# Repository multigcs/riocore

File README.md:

[LinuxCNC-RIO](https://github.com/multigcs/LinuxCNC-RIO) - rewrite

<h3 align="center">RIO</h3>

<div align="center">

</div>

---

<p align="center"> Realtime-IO for Motion-Control <br></p>

## Table of Contents
- [About](#about)
- [Disclaimer](#disclaimer)
- [Help](#help)
- [Boards](#boards)
- [Plugins/Drivers](#plugins)
- [supported Toolchains](#toolchains)
- [Getting Started](#getting_started)
- [Usage](#usage)
- [Flow](#flow)

## About 

RIO is a cost-effective and flexible alternative to traditional hardware setups like Mesa boards,
it's a code generator for using FPGA boards as Realtime-IO for LinuxCNC and other Motion-Control systems.

Furthermore, the complete configuration and hal is generated.
a json configuration file serves as the basis

* operates without a soft-core processor, relying solely on FPGA logic, which eliminates jitter and ensures fast, reliable performance
* It supports communication via SPI (e.g., with Raspberry Pi 4) or Ethernet, providing flexibility for different hardware setups
* Configuration is managed via JSON files, enabling easy customization of pin selection and other parameters. The tool automatically generates LinuxCNC configuration files (HAL/INI), saving significant setup time
* using free FPGA-Toolchain or commercial (depends on the FPGA)
* Compatible with a wide range of FPGA boards, including ICE40, ECP5, MAX10, Artix7, Gowin, CycloneIV, and TangNano9K, allowing users to choose hardware that fits their needs and budget
* Supports open and closed-loop control for multiple motor types (e.g., stepper motors, DC servos), as well as mixed joint configurations
* Primarily intended for LinuxCNC but also suitable for other systems such as ROS (Robot Operating System)

These features make RIO an attractive solution for hobbyists and professionals seeking a customizable, cost-effective Realtime-IO interface for Motion-Control systems

## DISCLAIMER 
THE AUTHORS OF THIS SOFTWARE ACCEPT ABSOLUTELY NO LIABILITY FOR ANY HARM OR LOSS RESULTING FROM ITS USE.
IT IS EXTREMELY UNWISE TO RELY ON SOFTWARE ALONE FOR SAFETY.
Any machinery capable of harming persons must have provisions
for completely removing power from all motors, etc, before persons enter any danger area.
All machinery must be designed to comply with local and national safety codes,
and the authors of this software can not,
and do not, take any responsibility for such compliance

## Help 

* [LinuxCNC-Forum (en)](https://forum.linuxcnc.org/18-computer/49142-linuxcnc-rio-realtimeio-for-linuxcnc-based-on-fpga-ice40-ecp5)
* [cnc-aus-holz (de)](https://www.cnc-aus-holz.at/)

## Boards 
list of all boards: [BOARDS](riocore/plugins/fpga/BOARDS.md)

## Plugins/Drivers 
list of all plugins: [PLUGINS](riocore/plugins/README.md)

## supported Toolchains 
list of all  toolchains: [TOOLCHAINS](riocore/plugins/fpga/generator/toolchains/README.md)

## Getting Started 

There are multiple ways of getting started. 

 1. Installer-Script (tested on debian bookworm and trixie)  [installer](#installer).
 2. Install riocore on the linux  [host](#host).
 3. Use [docker](doc/DOCKER.md).

### Installer-Script (debian-bookworm only) 
if you have a Debian-Bookworm installation (e.g. from the LinuxCNC ISO or the LinuxCNC raspberry image)
you can simply use this script to install all depends and the icestorm and gowin toolchain (gowin only on Intel/AMD)
```
wget -O- https://www.multixmedia.org/riocore-installer.sh | bash
```

### Install ricore on the host 

- installing via git:
```
git clone https://github.com/multigcs/riocore.git
cd riocore
```

- installing dependencies via apt:
```
apt-get update
apt-get -y install python3 python3-pip python3-yaml python3-graphviz python3-pyqtgraph python3-pyqt5 python3-pyqt5.qtsvg python3-lxml python3-psutil python3-spidev python3-magic
```

make sure that the toolchain matching your fpga is in the path:
```
export PATH=$PATH:/opt/oss-cad-suite/bin/
export PATH=$PATH:/opt/Xilinx/Vivado/2023.1/bin/
export PATH=$PATH:/opt/gowin/IDE/bin/
export PATH=$PATH:/opt/intelFPGA_lite/22.1std/quartus/bin/
export PATH=$PATH:/opt/Xilinx/14.7/ISE_DS/ISE/bin/lin64/
```

than copy a config file that is near to your setup:
```
cp riocore/configs/Tangoboard/config-spi.json my_config.json
```

## [DOCKER](doc/DOCKER.md) (alternative)

Using a TangNano9k or other board supported by the open-cad-suite? Check out the docker setup for an easy to use all in one way to run the riocore ui and generator, including flashing: [DOCKER](doc/DOCKER.md)

## Usage 

you can edit your configuration file by hand (text-editor) or using the config tool (rio-flow):
```
bin/rio-flow  riocore/configs/Tangbob/config.json
```

after setup, you can save your configuration and generate the output-files in the setup-tool via buttons:

* Generate : generates the output-files and write it into the './Output/' folder
* Compile: compiles the Bitfile for your FPGA
* Flash: writes the new bitfile onto the FPGA

you can also do this things on your console:

generate:
```
bin/rio-generator my_config.json
```
```
loading: my_config.json
loading board setup: TangNano9K
writing gateware to: Output/Tangoboard/Gateware
!!! gateware changed: needs to be built and flashed |||
loading toolchain gowin
writing linuxcnc files to: Output/Tangoboard/LinuxCNC
```
compile:
```
(
cd Output/BOARD_NAME/Gateware/
make clean all
)
```

flash:
```
(
cd Output/BOARD_NAME/Gateware/
make load
)
```

You can find all the LinuxCNC related files in 'Output/BOARD_NAME/LinuxCNC/',

to start LinuxCNC, you have to install the rio component first:
```
sudo halcompile --install riocore/files/rio.c
```

then you can start LinuxCNC with your new .ini file:
```
linuxcnc Output/BOARD_NAME/LinuxCNC/rio.ini
```

> [!WARNING]
> all files will be overwritte by the generator tool
> 
> if you change the .ini file by hand, for example, you should make a copy of it
> 
> if you need an additional .hal file, you can incude it in the postgui_call_list.hal
> 
> rio will not overwrite this entry's
>

### Prerequisites
you need the toolchain for your FPGA or in some cases the https://github.com/YosysHQ/oss-cad-suite-build

## Flow 

### Generator
```mermaid
graph LR;
    BOARD.JSON--rio-flow-->CONFIG.JSON;
    CONFIG.JSON--rio-generator-->/Output;
    /Output-->/Gateware;
    /Gateware-->Makefile;
    /Gateware-->verilog-files;
    /Gateware-->pins.*;
    Makefile--make-->Bitfile;
    Bitfile--make load-->FPGA;
    /Output-->/LinuxCNC;
    /LinuxCNC-->riocomp.c;
    /LinuxCNC-->rio.ini
    /LinuxCNC-->rio-gui.xml
    /LinuxCNC-->*.hal;
    /Output-->/ROS;
    /Output-->/MQTT;
    /Output-->/Simulator;
```

### LinuxCNC
```mermaid
graph LR;
    LinuxCNC<-->rio.c;
    rio.c<-->riocomp.c;
    riocomp.c<--UDP/SPI-->FPGA;
    FPGA<--RS422/RS485-->SUB_FPGA;
```

### ROS
```mermaid
graph LR;
    ROS-Plugin-1<--TCP-->ROS-core
    ROS-Plugin-2<--TCP-->ROS-core
    ROS-Plugin-N<--TCP-->ROS-core
    ROS-core<--TCP-->rosbridge;
    rosbridge<--UDP/SPI-->FPGA;
    FPGA<--RS422/RS485-->SUB_FPGA;
```

### MQTT
```mermaid
graph LR;
    HTML+JS<--Websockets-->MQTT-Broker
    MQTT-Client-1<--MQTT-->MQTT-Broker
    MQTT-Client-2<--MQTT-->MQTT-Broker
    MQTT-Client-N<--MQTT-->MQTT-Broker
    MQTT-Broker<--MQTT-->mqttbridge;
    mqttbridge<--UDP/SPI-->FPGA;
    FPGA<--RS422/RS485-->SUB_FPGA;
```

### JSLIB
```mermaid
graph LR;
    nodejs<-->JSLIB
    JSLIB<--UDP-->FPGA;
    FPGA<--RS422/RS485-->SUB_FPGA;
```

## Directory Structure

### Source
```
riocore
├── bin ················ user tools / gui's
├── doc ················ documentation
├── dockerfiles ········ files to run the docker container
├┬─ ricore ············· main directory 
|├── configs ··········· some demo configurations
|├── gui ··············· widgets and functions for the gui tools
|├── files ············· helper scripts and files
|├── generator ········ the generator for the LinuxCNC configuration
|├── plugins ··········· location of the plugins
├── tests ·············· unit tests
```

### Generated Output
```
Output
├┬─ BOARD_NAME ········· for each board
|├── Gateware ·········· Gateware-Files for the FPGA
|├── LinuxCNC ·········· LinuxCNC configuration (hal/ini/component)
|├── PYLIB ············· C and Python lib with testgui.py
|├── MQTT ·············· MQTT-Bridge
|├── ROS ··············· ROS-Bridge
|├── Simulator ········· Simulator-Sources
|├── JSLIB ············· Javascrit lib
|├── DOC ··············· some Documentation files
```

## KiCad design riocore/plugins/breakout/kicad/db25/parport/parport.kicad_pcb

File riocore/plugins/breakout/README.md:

# breakout

**5Axis China-BOB**

* NEEDS: db25

## Node-Types
| Name | Image |
| --- | --- |
| china-bob5x |  |
| db25-1205 |  |
| db25 |  |
| rio-icebreaker3x |  |
| rioctrl-quadenc4 |  |
| rioctrl-shiftio |  |
| rioctrl-stepdir |  |
| rpi-db25hat |  |

## Pins:
*FPGA-pins*
### SLOT:P1:

 * direction: all
 * optional: True

### SLOT:P2:

 * direction: all
 * optional: True

### SLOT:P3:

 * direction: all
 * optional: True

### SLOT:P4:

 * direction: all
 * optional: True

### SLOT:P5:

 * direction: all
 * optional: True

### SLOT:P6:

 * direction: all
 * optional: True

### SLOT:P7:

 * direction: all
 * optional: True

### SLOT:P8:

 * direction: all
 * optional: True

### SLOT:P9:

 * direction: all
 * optional: True

### SLOT:P10:

 * direction: all
 * optional: True

### SLOT:P11:

 * direction: all
 * optional: True

### SLOT:P12:

 * direction: all
 * optional: True

### SLOT:P13:

 * direction: all
 * optional: True

### SLOT:P14:

 * direction: all
 * optional: True

### SLOT:P15:

 * direction: all
 * optional: True

### SLOT:P16:

 * direction: all
 * optional: True

### SLOT:P17:

 * direction: all
 * optional: True

### OPTO:in0:

 * direction: input
 * optional: True

### OPTO:in1:

 * direction: input
 * optional: True

### OPTO:in2:

 * direction: input
 * optional: True

### OPTO:in3:

 * direction: input
 * optional: True

### OPTO:in4:

 * direction: input
 * optional: True

### RELAIS:out:

 * direction: output
 * optional: True

### POWER:5V_1:

 * direction: none
 * optional: True

### POWER:5V_2:

 * direction: none
 * optional: True

### POWER:GND:

 * direction: none
 * optional: True

### POWER:F_GND_1:

 * direction: none
 * optional: True

### POWER:F_GND_2:

 * direction: none
 * optional: True

### POWER:F_24V:

 * direction: none
 * optional: True

### POWER:F_GND_3:

 * direction: none
 * optional: True

### PWM:analog:

 * direction: output
 * optional: True

### PWM:digital:

 * direction: output
 * optional: True

### B:dir:

 * direction: output
 * optional: True

### B:step:

 * direction: output
 * optional: True

### ALL:en:

 * direction: output
 * optional: True

### A:dir:

 * direction: output
 * optional: True

### A:step:

 * direction: output
 * optional: True

### Z:dir:

 * direction: output
 * optional: True

### Z:step:

 * direction: output
 * optional: True

### Y:dir:

 * direction: output
 * optional: True

### Y:step:

 * direction: output
 * optional: True

### X:dir:

 * direction: output
 * optional: True

### X:step:

 * direction: output
 * optional: True

## Options:
*user-options*
### name:
name of this plugin instance

 * type: str
 * default: 

### image:
hardware type

 * type: imgselect
 * default: generic

### node_type:
board type

 * type: select
 * default: china-bob5x
 * options: china-bob5x, db25-1205, db25, rio-icebreaker3x, rioctrl-quadenc4, rioctrl-shiftio, rioctrl-stepdir, rpi-db25hat

## Signals:
*signals/pins in LinuxCNC*

## Interfaces:
*transport layer*

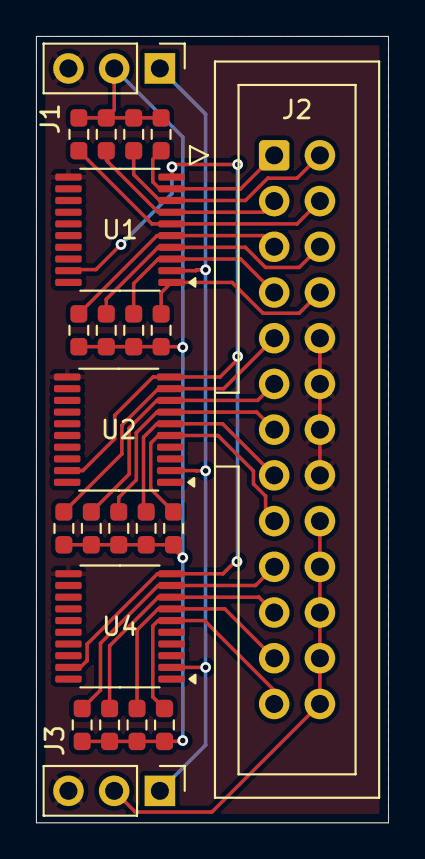
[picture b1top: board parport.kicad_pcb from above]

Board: 2 copper layers, 19.6 x 43.7 mm, 23 parts (0 on the bottom side), 22 nets.

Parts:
J1, J3: Conn_01x03; PinHeader_1x03_P2.54mm_Vertical
J2: Conn_02x13_Odd_Even; IDC-Header_2x13_P2.54mm_Vertical
R1, R2, R3, R4, R5, R6, R7, R8, R9, R10, R11, R12, R13, R14, R15, R16, R17: 10k; R_0603_1608Metric_Pad0.98x0.95mm_HandSolder
U1, U2, U4: TXS0108EPW; TSSOP-20_4.4x6.5mm_P0.65mm

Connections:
3V3: U1.10 (OE), U1.19 (VCCB), U2.10 (OE), U2.19 (VCCB), U4.10 (OE), U4.19 (VCCB)
5V: J1.1, J3.1, U1.2 (VCCA), U2.2 (VCCA), U4.2 (VCCA)
GND: J1.3, J2.10, J2.12, J2.14, J2.16, J3.3, U1.11 (GND), U2.11 (GND), U4.11 (GND)
unnamed: J1.2, R1.1, R2.1, R3.1, R4.1, R5.1, R6.1, R7.1, R8.1, R9.1, R10.1, R11.1, R12.1, R13.1, R14.1, R15.1, R16.1, R17.1
unnamed: J2.1, R12.2, U1.9 (A8)
unnamed: J2.2, R1.2, U1.8 (A7)
unnamed: J2.3, R2.2, U1.7 (A6)
unnamed: J2.4, R3.2, U1.6 (A5)
unnamed: J2.5, R4.2, U1.5 (A4)
unnamed: J2.6, R5.2, U1.4 (A3)
unnamed: J2.7, R6.2, U1.3 (A2)
unnamed: J2.8, R7.2, U1.1 (A1)
unnamed: J2.9, R8.2, U2.9 (A8)
unnamed: J2.11, R9.2, U2.8 (A7)
unnamed: J2.13, R10.2, U2.7 (A6)
unnamed: J2.15, R11.2, U2.6 (A5)
unnamed: J2.17, R13.2, U2.5 (A4)
unnamed: J2.18, J2.20, J2.22, J2.24, J2.26, J3.2
unnamed: J2.19, R14.2, U4.9 (A8)
unnamed: J2.21, R15.2, U4.8 (A7)
unnamed: J2.23, R16.2, U4.7 (A6)
unnamed: J2.25, R17.2, U4.6 (A5)

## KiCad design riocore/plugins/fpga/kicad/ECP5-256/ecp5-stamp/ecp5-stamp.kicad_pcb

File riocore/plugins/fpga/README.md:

# fpga
**fpga board**

fpga

* Keywords: fpga board
* PROVIDES: fpga, base

## Node-Types
| Name | Image |
| --- | --- |
| Altera10M08Eval |  |
| Arty-a7-35t |  |
| Basys2 |  |
| CYC1000 |  |
| CarrotBob |  |
| Colorlight5A-75B-v8.0 |  |
| Colorlight5A-75E |  |
| Colorlight_i5-v7_0 |  |
| Core3S250E |  |
| EBAZ4205 |  |
| ECP5-256 |  |
| EP2C5T144 |  |
| EP4CE6E22C8 |  |
| EPM240 |  |
| EPM240mini |  |
| ICEBreakerV1.0e |  |
| ICESugarNano |  |
| ICESugarPro |  |
| IceShield |  |
| LX9MicroBoard |  |
| Mesa7c81 |  |
| MotoMan |  |
| Numato-Spartan6 |  |
| OctoBot |  |
| Olimex-ICE40HX8K-EVB |  |
| ShrikeLite |  |
| Spartan6 | - |
| TangNano1K |  |
| TangNano20K |  |
| TangNano4K |  |
| TangNano9K |  |
| TangPrimer20K |  |
| TangPrimer25K |  |
| Tangbob |  |
| Tangoboard |  |
| XC9536XL |  |
| iCESugar1.5 |  |
| rioctrl |  |

## Pins:
*FPGA-pins*

## Options:
*user-options*
### name:
name of this plugin instance

 * type: str
 * default: 

### image:
hardware type

 * type: imgselect
 * default: generic

### node_type:
board type

 * type: select
 * default: 
 * options: Altera10M08Eval, Arty-a7-35t, Basys2, CYC1000, CarrotBob, Colorlight5A-75B-v8.0, Colorlight5A-75E, Colorlight_i5-v7_0, Core3S250E, EBAZ4205, ECP5-256, EP2C5T144, EP4CE6E22C8, EPM240, EPM240mini, ICEBreakerV1.0e, ICESugarNano, ICESugarPro, IceShield, LX9MicroBoard, Mesa7c81, MotoMan, Numato-Spartan6, OctoBot, Olimex-ICE40HX8K-EVB, ShrikeLite, Spartan6, TangNano1K, TangNano20K, TangNano4K, TangNano9K, TangPrimer20K, TangPrimer25K, Tangbob, Tangoboard, XC9536XL, iCESugar1.5, rioctrl

### simulation:
simulation mode

 * type: bool
 * default: False

## Signals:
*signals/pins in LinuxCNC*

## Interfaces:
*transport layer*

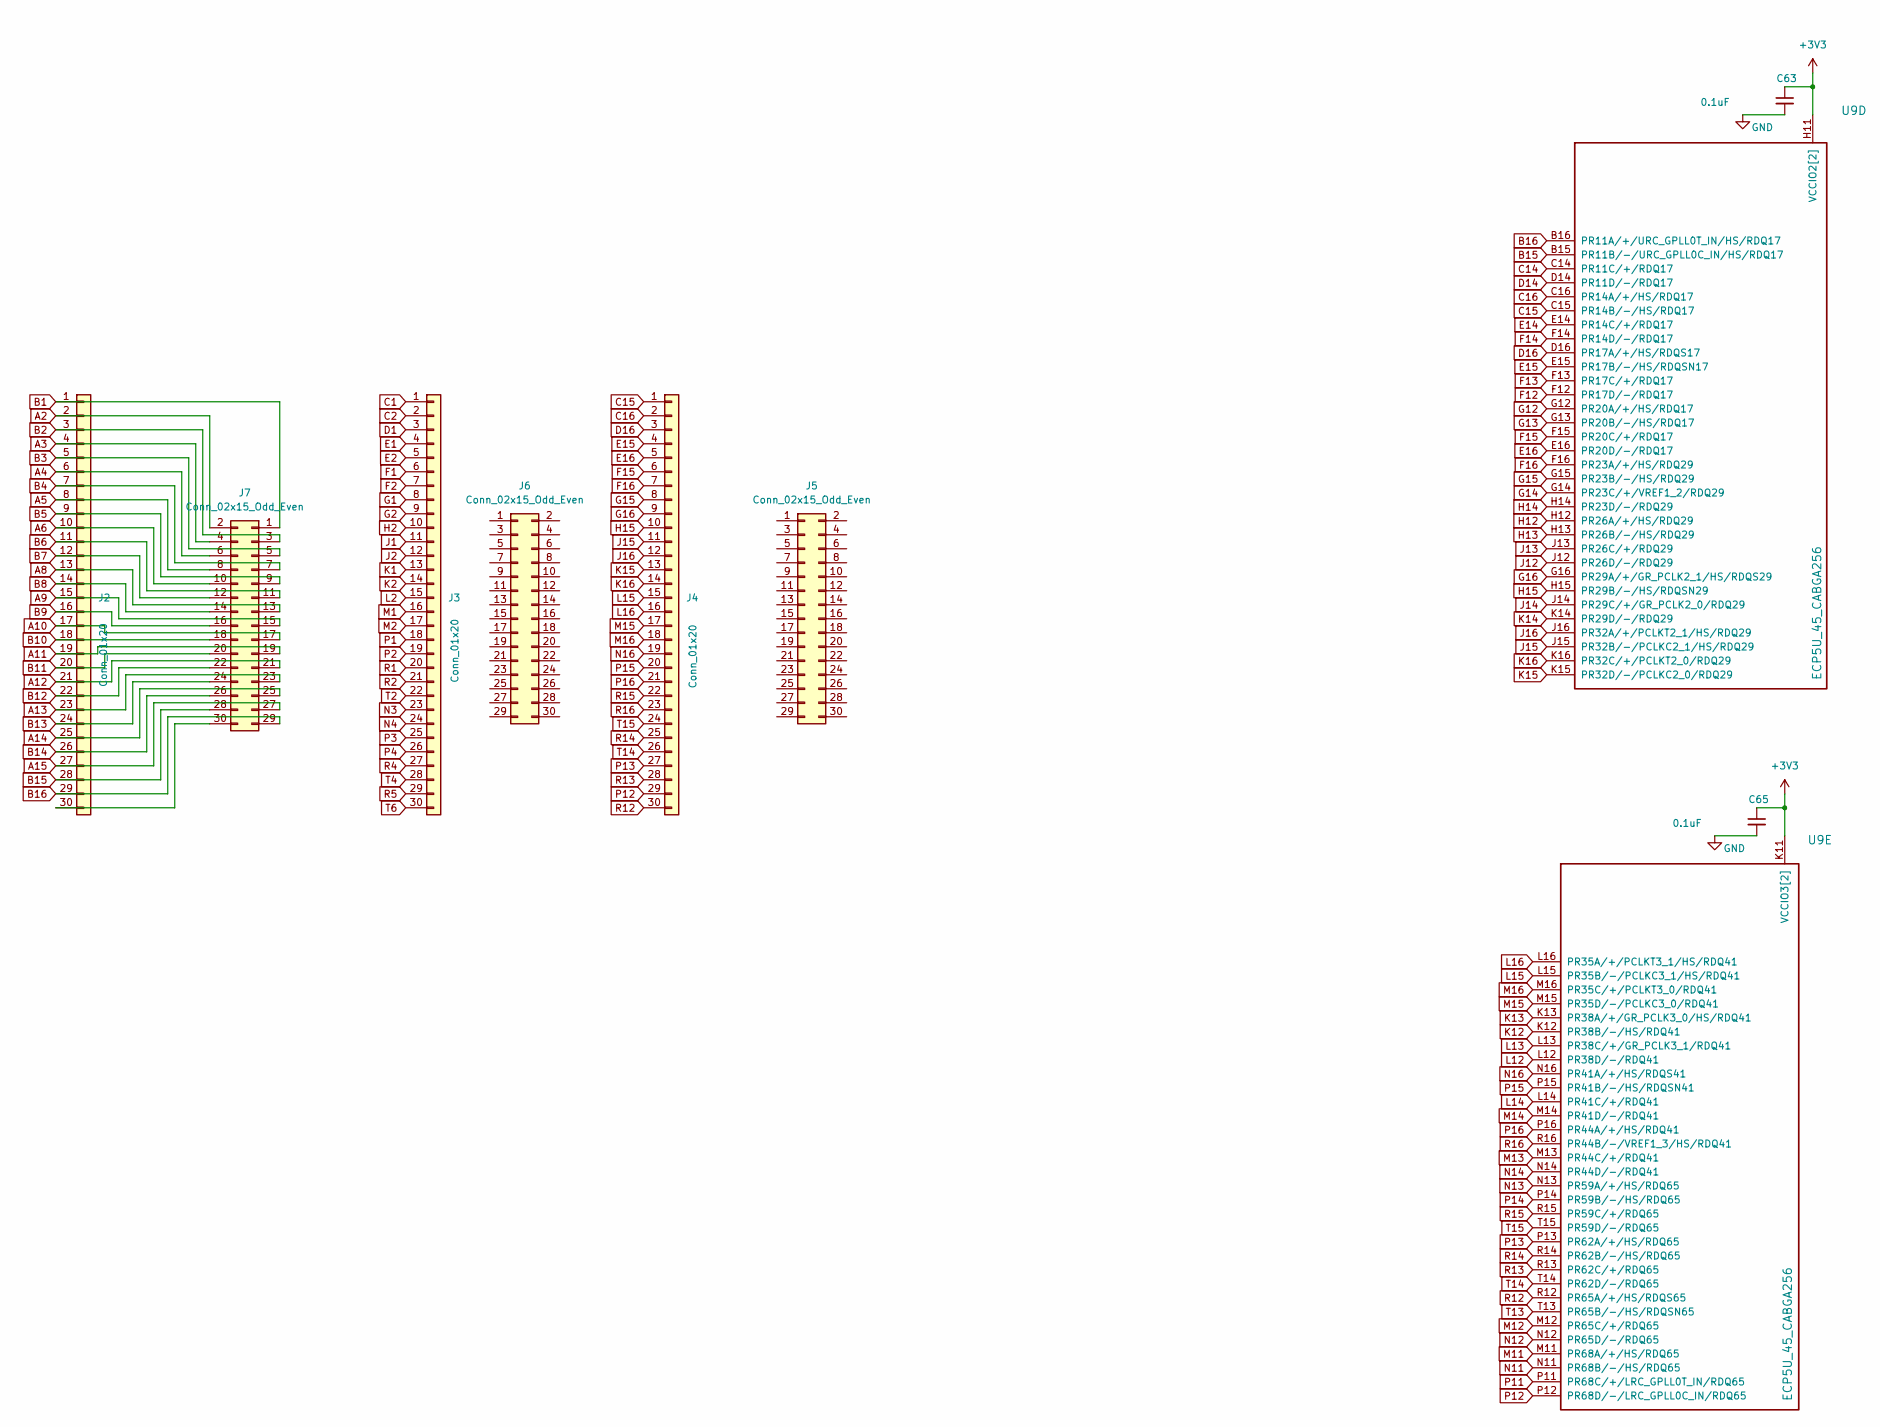
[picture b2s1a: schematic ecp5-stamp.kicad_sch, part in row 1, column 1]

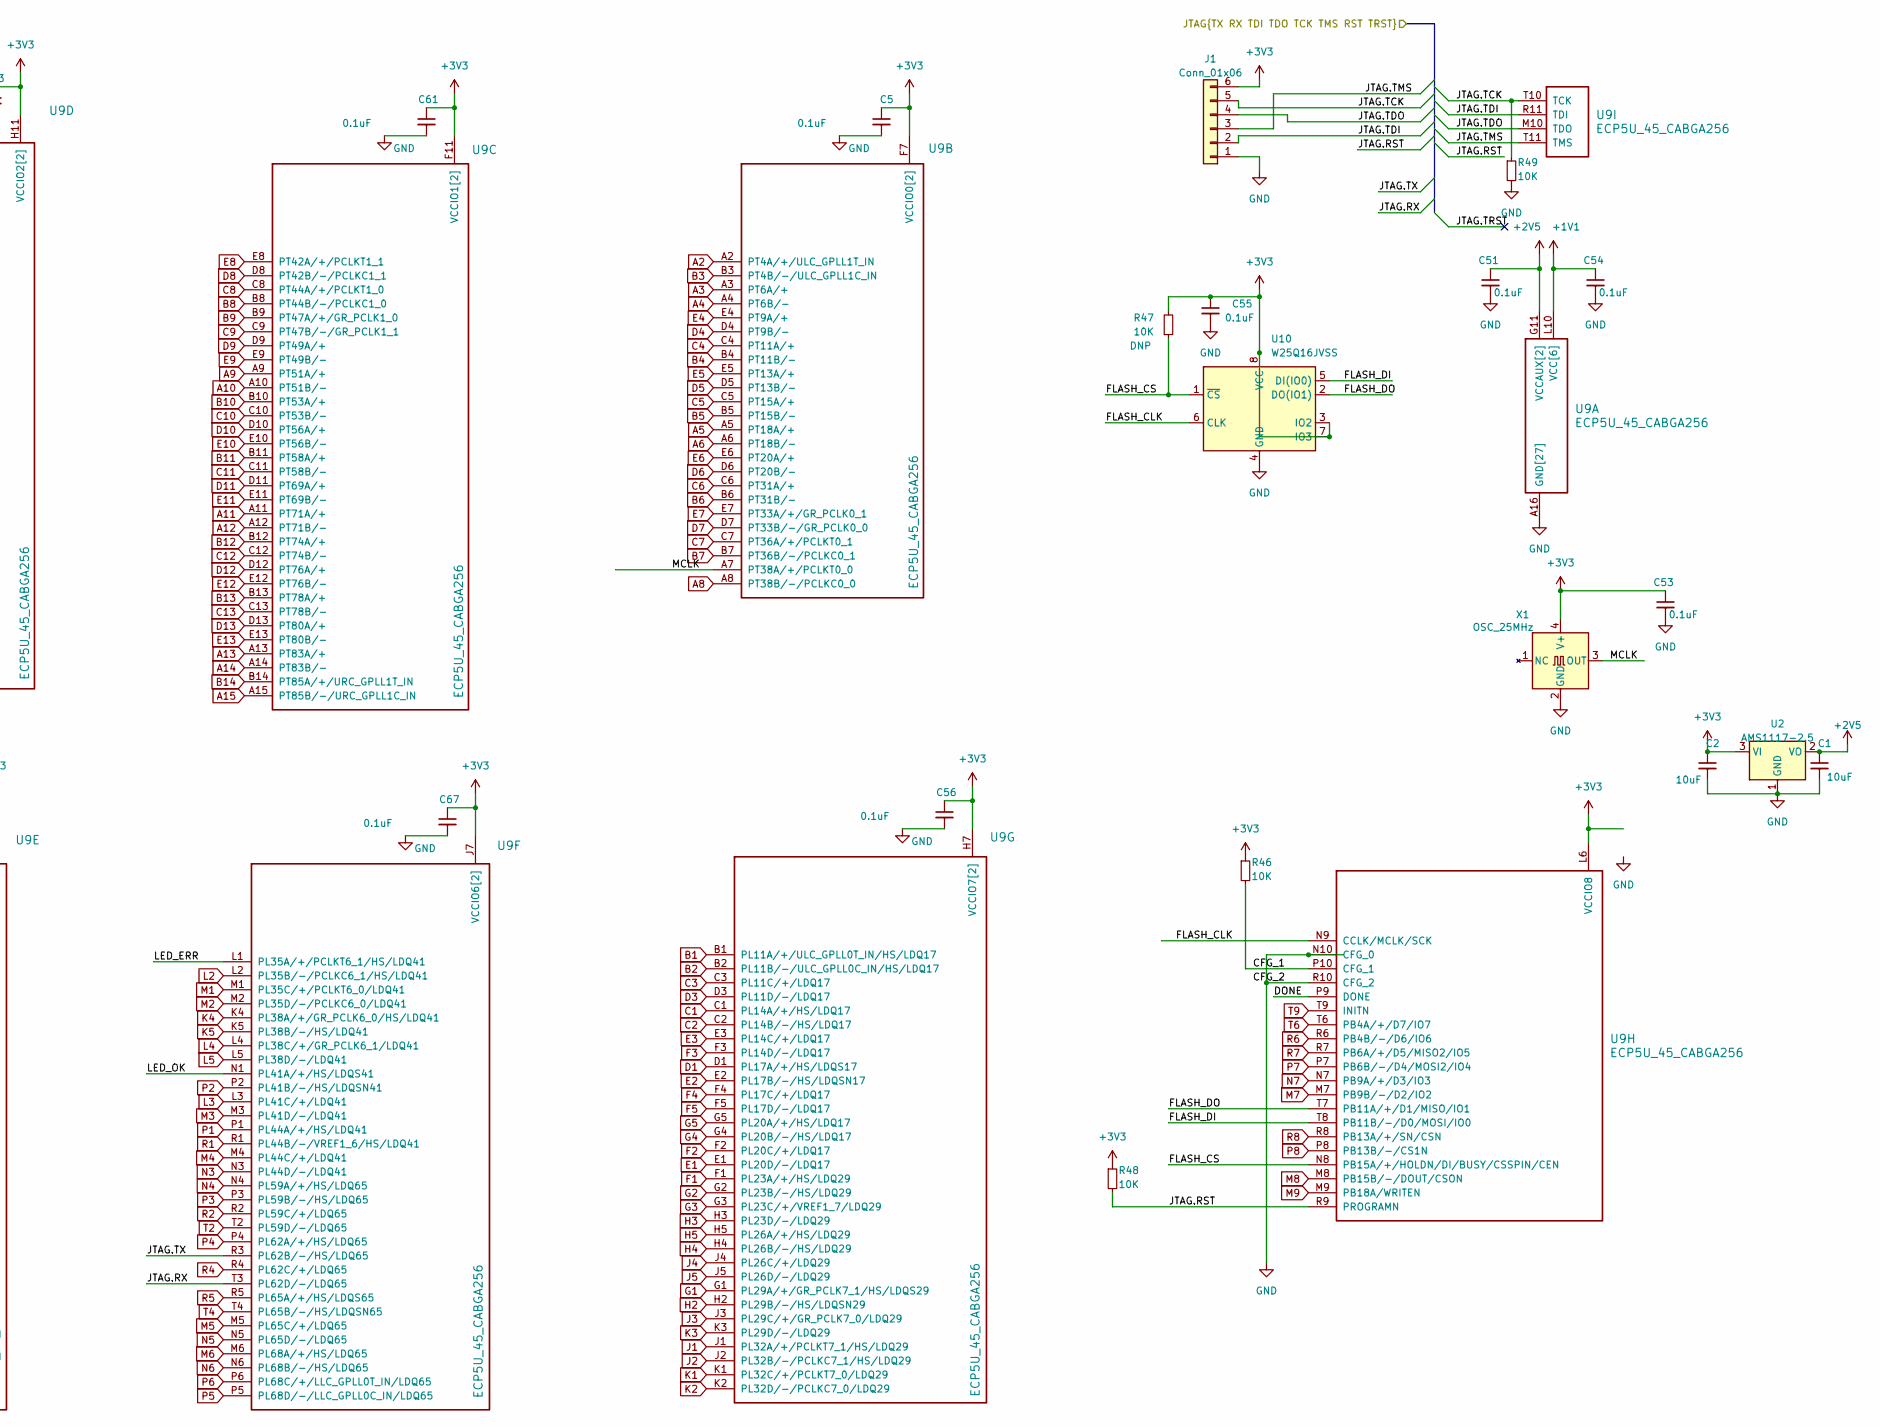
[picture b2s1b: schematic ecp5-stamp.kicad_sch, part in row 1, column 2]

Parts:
C1, C2: 10uF; C_0805_2012Metric; LCSC# C56392
C5, C51, C53, C54, C56, C61, C63, C65, C67: 0.1uF; C_0805_2012Metric; LCSC# C56392
C55: 0.1uF; C_0805_2012Metric; MPN CC0603KRX7R9BB104; LCSC# C14663
J1: Conn_01x06; PinHeader_1x06_P1.27mm_Vertical
J2, J3, J4: Conn_01x20; PinHeader_1x30_P1.27mm_Vertical
J5, J6: Conn_02x15_Odd_Even
J7: Conn_02x15_Odd_Even; PinHeader_2x15_P2.54mm_Vertical
R46, R48, R49: 10K; R_0603_1608Metric; LCSC# C98220
R47: 10K; R_0603_1608Metric; MPN RC0603FR-0710KL; LCSC# C98220
U2: AMS1117-2.5; SOT-223-3_TabPin2
U9: ECP5U_45_CABGA256; BGA-256_14.0x14.0mm_Layout16x16_P0.8mm_Ball0.45mm_Pad0.32mm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; MPN LFE5U-12F-6BG256C; LCSC# C1550762
U10: W25Q16JVSS; SOIC-8_5.3x5.3mm_P1.27mm; MPN W25Q16JVSSIQ; LCSC# C82317
X1: OSC_25MHz; Oscillator_SMD_EuroQuartz_XO32-4Pin_3.2x2.5mm; MPN OT322525MJBA4SL; LCSC# C669088

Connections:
+1V1: C54.1, U9.G6 (VCC[6]), U9.G7 (VCC[6]), U9.G9 (VCC[6]), U9.L8 (VCC[6]), U9.L9 (VCC[6]), U9.L10 (VCC[6])
+2V5: C1.1, C51.1, U2.2 (VO), U9.G11 (VCCAUX[2]), U9.L7 (VCCAUX[2])
+3V3: C2.1, C5.1, C53.1, C55.1, C56.1, C61.1, C63.1, C65.1, C67.1, J1.6, R46.1, R47.2, R48.1, U2.3 (VI), U9.F6 (VCCIO0[2]), U9.F7 (VCCIO0[2]), U9.F10 (VCCIO1[2]), U9.F11 (VCCIO1[2]), U9.H6 (VCCIO7[2]), U9.H7 (VCCIO7[2]), U9.H11 (VCCIO2[2]), U9.J6 (VCCIO6[2]), U9.J7 (VCCIO6[2]), U9.J11 (VCCIO2[2]), U9.K11 (VCCIO3[2]), U9.L6 (VCCIO8), U9.L11 (VCCIO3[2]), U10.3 (IO2), U10.7 (IO3), U10.8 (VCC), X1.4 (V+)
/CFG_1: R46.2, U9.P10 (CFG_1)
/DONE: U9.P9 (DONE)
/FLASH_CLK: U9.N9 (CCLK/MCLK/SCK), U10.6 (CLK)
/FLASH_CS: R47.1, U9.N8 (PB15A/+/HOLDN/DI/BUSY/CSSPIN/CEN), U10.1 (~CS)
/FLASH_DI: U9.T8 (PB11B/-/D0/MOSI/IO0), U10.5 (DI(IO0))
/FLASH_DO: U9.T7 (PB11A/+/D1/MISO/IO1), U10.2 (DO(IO1))
/JTAG.RST: R48.2, U9.R9 (PROGRAMN)
/JTAG.RX: U9.T3 (PL62D/-/LDQ65)
/JTAG.TCK: J1.5, R49.1, U9.T10 (TCK)
/JTAG.TDI: J1.2, U9.R11 (TDI)
/JTAG.TDO: J1.4, U9.M10 (TDO)
/JTAG.TMS: J1.3, U9.T11 (TMS)
/JTAG.TX: U9.R3 (PL62B/-/HS/LDQ65)
/LED_ERR: U9.L1 (PL35A/+/PCLKT6_1/HS/LDQ41)
/LED_OK: U9.N1 (PL41A/+/HS/LDQS41)
/MCLK: U9.A7 (PT38A/+/PCLKT0_0), X1.3 (OUT)
A2: J2.2, J7.2, U9.A2 (PT4A/+/ULC_GPLL1T_IN)
A3: J2.4, J7.4, U9.A3 (PT6A/+)
A4: J2.6, J7.6, U9.A4 (PT6B/-)
A5: J2.8, J7.8, U9.A5 (PT18A/+)
A6: J2.10, J7.10, U9.A6 (PT18B/-)
A8: J2.13, J7.13, U9.A8 (PT38B/-/PCLKC0_0)
A9: J2.15, J7.15, U9.A9 (PT51A/+)
A10: J2.17, J7.17, U9.A10 (PT51B/-)
A11: J2.19, J7.19, U9.A11 (PT71A/+)
A12: J2.21, J7.21, U9.A12 (PT71B/-)
A13: J2.23, J7.23, U9.A13 (PT83A/+)
A14: J2.25, J7.25, U9.A14 (PT83B/-)
A15: J2.27, J7.27, U9.A15 (PT85B/-/URC_GPLL1C_IN)
B1: J2.1, J7.1, U9.B1 (PL11A/+/ULC_GPLL0T_IN/HS/LDQ17)
B2: J2.3, J7.3, U9.B2 (PL11B/-/ULC_GPLL0C_IN/HS/LDQ17)
B3: J2.5, J7.5, U9.B3 (PT4B/-/ULC_GPLL1C_IN)
B4: J2.7, J7.7, U9.B4 (PT11B/-)
B5: J2.9, J7.9, U9.B5 (PT15B/-)
B6: J2.11, J7.11, U9.B6 (PT31B/-)
B7: J2.12, J7.12, U9.B7 (PT36B/-/PCLKC0_1)
B8: J2.14, J7.14, U9.B8 (PT44B/-/PCLKC1_0)
B9: J2.16, J7.16, U9.B9 (PT47A/+/GR_PCLK1_0)
B10: J2.18, J7.18, U9.B10 (PT53A/+)
B11: J2.20, J7.20, U9.B11 (PT58A/+)
B12: J2.22, J7.22, U9.B12 (PT74A/+)
B13: J2.24, J7.24, U9.B13 (PT78A/+)
B14: J2.26, J7.26, U9.B14 (PT85A/+/URC_GPLL1T_IN)
B15: J2.28, J7.28, U9.B15 (PR11B/-/URC_GPLL0C_IN/HS/RDQ17)
B16: J2.29, J7.29, U9.B16 (PR11A/+/URC_GPLL0T_IN/HS/RDQ17)
C1: J3.1, U9.C1 (PL14A/+/HS/LDQ17)
C2: J3.2, U9.C2 (PL14B/-/HS/LDQ17)
C3: U9.C3 (PL11C/+/LDQ17)
C4: U9.C4 (PT11A/+)
C5: U9.C5 (PT15A/+)
C6: U9.C6 (PT31A/+)
C7: U9.C7 (PT36A/+/PCLKT0_1)
C8: U9.C8 (PT44A/+/PCLKT1_0)
C9: U9.C9 (PT47B/-/GR_PCLK1_1)
C10: U9.C10 (PT53B/-)
C11: U9.C11 (PT58B/-)
C12: U9.C12 (PT74B/-)
C13: U9.C13 (PT78B/-)
C14: U9.C14 (PR11C/+/RDQ17)
C15: J4.1, U9.C15 (PR14B/-/HS/RDQ17)
C16: J4.2, U9.C16 (PR14A/+/HS/RDQ17)
D1: J3.3, U9.D1 (PL17A/+/HS/LDQS17)
D3: U9.D3 (PL11D/-/LDQ17)
D4: U9.D4 (PT9B/-)
D5: U9.D5 (PT13B/-)
D6: U9.D6 (PT20B/-)
D7: U9.D7 (PT33B/-/GR_PCLK0_0)
D8: U9.D8 (PT42B/-/PCLKC1_1)
D9: U9.D9 (PT49A/+)
D10: U9.D10 (PT56A/+)
D11: U9.D11 (PT69A/+)
D12: U9.D12 (PT76A/+)
D13: U9.D13 (PT80A/+)
D14: U9.D14 (PR11D/-/RDQ17)
D16: J4.3, U9.D16 (PR17A/+/HS/RDQS17)
E1: J3.4, U9.E1 (PL20D/-/LDQ17)
E2: J3.5, U9.E2 (PL17B/-/HS/LDQSN17)
E3: U9.E3 (PL14C/+/LDQ17)
E4: U9.E4 (PT9A/+)
E5: U9.E5 (PT13A/+)
E6: U9.E6 (PT20A/+)
E7: U9.E7 (PT33A/+/GR_PCLK0_1)
E8: U9.E8 (PT42A/+/PCLKT1_1)
E9: U9.E9 (PT49B/-)
E10: U9.E10 (PT56B/-)
E11: U9.E11 (PT69B/-)
E12: U9.E12 (PT76B/-)
E13: U9.E13 (PT80B/-)
E14: U9.E14 (PR14C/+/RDQ17)
E15: J4.4, U9.E15 (PR17B/-/HS/RDQSN17)
E16: J4.5, U9.E16 (PR20D/-/RDQ17)
F1: J3.6, U9.F1 (PL23A/+/HS/LDQ29)
F2: J3.7, U9.F2 (PL20C/+/LDQ17)
F3: U9.F3 (PL14D/-/LDQ17)
F4: U9.F4 (PL17C/+/LDQ17)
F5: U9.F5 (PL17D/-/LDQ17)
F12: U9.F12 (PR17D/-/RDQ17)
F13: U9.F13 (PR17C/+/RDQ17)
F14: U9.F14 (PR14D/-/RDQ17)
F15: J4.6, U9.F15 (PR20C/+/RDQ17)
F16: J4.7, U9.F16 (PR23A/+/HS/RDQ29)
G1: J3.8, U9.G1 (PL29A/+/GR_PCLK7_1/HS/LDQS29)
G2: J3.9, U9.G2 (PL23B/-/HS/LDQ29)
G3: U9.G3 (PL23C/+/VREF1_7/LDQ29)
G4: U9.G4 (PL20B/-/HS/LDQ17)
G5: U9.G5 (PL20A/+/HS/LDQ17)
G12: U9.G12 (PR20A/+/HS/RDQ17)
G13: U9.G13 (PR20B/-/HS/RDQ17)
G14: U9.G14 (PR23C/+/VREF1_2/RDQ29)
G15: J4.8, U9.G15 (PR23B/-/HS/RDQ29)
G16: J4.9, U9.G16 (PR29A/+/GR_PCLK2_1/HS/RDQS29)
GND: C1.2, C2.2, C5.2, C51.2, C53.2, C54.2, C55.2, C56.2, C61.2, C63.2, C65.2, C67.2, J1.1, R49.2, U2.1 (GND), U9.A1 (GND[27]), U9.A16 (GND[27]), U9.D2 (GND[27]), U9.D15 (GND[27]), U9.F8 (GND[27]), U9.F9 (GND[27]), U9.G8 (GND[27]), U9.G10 (GND[27]), U9.H1 (GND[27]), U9.H8 (GND[27]), U9.H9 (GND[27]), U9.H10 (GND[27]), U9.H16 (GND[27]), U9.J8 (GND[27]), U9.J9 (GND[27]), U9.J10 (GND[27]), U9.K6 (GND[27]), U9.K7 (GND[27]), U9.K8 (GND[27]), U9.K9 (GND[27]), U9.K10 (GND[27]), U9.N2 (GND[27]), U9.N10 (CFG_0), U9.N15 (GND[27]), U9.R10 (CFG_2), U9.T1 (GND[27]), U9.T5 (GND[27]), U9.T12 (GND[27]), U9.T16 (GND[27]), U10.4 (GND), X1.2 (GND)
H2: J3.10, U9.H2 (PL29B/-/HS/LDQSN29)
H3: U9.H3 (PL23D/-/LDQ29)
H4: U9.H4 (PL26B/-/HS/LDQ29)
H5: U9.H5 (PL26A/+/HS/LDQ29)
H12: U9.H12 (PR26A/+/HS/RDQ29)
H13: U9.H13 (PR26B/-/HS/RDQ29)
H14: U9.H14 (PR23D/-/RDQ29)
H15: J4.10, U9.H15 (PR29B/-/HS/RDQSN29)
J1: J3.11, U9.J1 (PL32A/+/PCLKT7_1/HS/LDQ29)
J2: J3.12, U9.J2 (PL32B/-/PCLKC7_1/HS/LDQ29)
J3: U9.J3 (PL29C/+/GR_PCLK7_0/LDQ29)
J4: U9.J4 (PL26C/+/LDQ29)
J5: U9.J5 (PL26D/-/LDQ29)
J12: U9.J12 (PR26D/-/RDQ29)
J13: U9.J13 (PR26C/+/RDQ29)
J14: U9.J14 (PR29C/+/GR_PCLK2_0/RDQ29)
J15: J4.11, U9.J15 (PR32B/-/PCLKC2_1/HS/RDQ29)
J16: J4.12, U9.J16 (PR32A/+/PCLKT2_1/HS/RDQ29)
K1: J3.13, U9.K1 (PL32C/+/PCLKT7_0/LDQ29)
K2: J3.14, U9.K2 (PL32D/-/PCLKC7_0/LDQ29)
K3: U9.K3 (PL29D/-/LDQ29)
K4: U9.K4 (PL38A/+/GR_PCLK6_0/HS/LDQ41)
K5: U9.K5 (PL38B/-/HS/LDQ41)
K12: U9.K12 (PR38B/-/HS/RDQ41)
K13: U9.K13 (PR38A/+/GR_PCLK3_0/HS/RDQ41)
K14: U9.K14 (PR29D/-/RDQ29)
K15: J4.13, U9.K15 (PR32D/-/PCLKC2_0/RDQ29)
K16: J4.14, U9.K16 (PR32C/+/PCLKT2_0/RDQ29)
L2: J3.15, U9.L2 (PL35B/-/PCLKC6_1/HS/LDQ41)
L3: U9.L3 (PL41C/+/LDQ41)
L4: U9.L4 (PL38C/+/GR_PCLK6_1/LDQ41)
L5: U9.L5 (PL38D/-/LDQ41)
L12: U9.L12 (PR38D/-/RDQ41)
L13: U9.L13 (PR38C/+/GR_PCLK3_1/RDQ41)
L14: U9.L14 (PR41C/+/RDQ41)
L15: J4.15, U9.L15 (PR35B/-/PCLKC3_1/HS/RDQ41)
L16: J4.16, U9.L16 (PR35A/+/PCLKT3_1/HS/RDQ41)
M1: J3.16, U9.M1 (PL35C/+/PCLKT6_0/LDQ41)
M2: J3.17, U9.M2 (PL35D/-/PCLKC6_0/LDQ41)
M3: U9.M3 (PL41D/-/LDQ41)
M4: U9.M4 (PL44C/+/LDQ41)
M5: U9.M5 (PL65C/+/LDQ65)
M6: U9.M6 (PL68A/+/HS/LDQ65)
M7: U9.M7 (PB9B/-/D2/IO2)
M8: U9.M8 (PB15B/-/DOUT/CSON)
M9: U9.M9 (PB18A/WRITEN)
M11: U9.M11 (PR68A/+/HS/RDQ65)
M12: U9.M12 (PR65C/+/RDQ65)
M13: U9.M13 (PR44C/+/RDQ41)
M14: U9.M14 (PR41D/-/RDQ41)
M15: J4.17, U9.M15 (PR35D/-/PCLKC3_0/RDQ41)
M16: J4.18, U9.M16 (PR35C/+/PCLKT3_0/RDQ41)
N3: J3.23, U9.N3 (PL44D/-/LDQ41)
N4: J3.24, U9.N4 (PL59A/+/HS/LDQ65)
N5: U9.N5 (PL65D/-/LDQ65)
N6: U9.N6 (PL68B/-/HS/LDQ65)
N7: U9.N7 (PB9A/+/D3/IO3)
N11: U9.N11 (PR68B/-/HS/RDQ65)
N12: U9.N12 (PR65D/-/RDQ65)
N13: U9.N13 (PR59A/+/HS/RDQ65)
N14: U9.N14 (PR44D/-/RDQ41)
N16: J4.19, U9.N16 (PR41A/+/HS/RDQS41)
unnamed: J2.30, J7.30
P1: J3.18, U9.P1 (PL44A/+/HS/LDQ41)
P2: J3.19, U9.P2 (PL41B/-/HS/LDQSN41)
P3: J3.25, U9.P3 (PL59B/-/HS/LDQ65)
P4: J3.26, U9.P4 (PL62A/+/HS/LDQ65)
P5: U9.P5 (PL68D/-/LLC_GPLL0C_IN/LDQ65)
P6: U9.P6 (PL68C/+/LLC_GPLL0T_IN/LDQ65)
P7: U9.P7 (PB6B/-/D4/MOSI2/IO4)
P8: U9.P8 (PB13B/-/CS1N)
P11: U9.P11 (PR68C/+/LRC_GPLL0T_IN/RDQ65)
P12: J4.29, U9.P12 (PR68D/-/LRC_GPLL0C_IN/RDQ65)
P13: J4.27, U9.P13 (PR62A/+/HS/RDQ65)
P14: U9.P14 (PR59B/-/HS/RDQ65)
P15: J4.20, U9.P15 (PR41B/-/HS/RDQSN41)
P16: J4.21, U9.P16 (PR44A/+/HS/RDQ41)
R1: J3.20, U9.R1 (PL44B/-/VREF1_6/HS/LDQ41)
R2: J3.21, U9.R2 (PL59C/+/LDQ65)
R4: J3.27, U9.R4 (PL62C/+/LDQ65)
R5: J3.29, U9.R5 (PL65A/+/HS/LDQS65)
R6: U9.R6 (PB4B/-/D6/IO6)
R7: U9.R7 (PB6A/+/D5/MISO2/IO5)
R8: U9.R8 (PB13A/+/SN/CSN)
R12: J4.30, U9.R12 (PR65A/+/HS/RDQS65)
R13: J4.28, U9.R13 (PR62C/+/RDQ65)
R14: J4.25, U9.R14 (PR62B/-/HS/RDQ65)
R15: J4.22, U9.R15 (PR59C/+/RDQ65)
R16: J4.23, U9.R16 (PR44B/-/VREF1_3/HS/RDQ41)
T2: J3.22, U9.T2 (PL59D/-/LDQ65)
T4: J3.28, U9.T4 (PL65B/-/HS/LDQSN65)
T6: J3.30, U9.T6 (PB4A/+/D7/IO7)
T9: U9.T9 (INITN)
T13: U9.T13 (PR65B/-/HS/RDQSN65)
T14: J4.26, U9.T14 (PR62D/-/RDQ65)
T15: J4.24, U9.T15 (PR59D/-/RDQ65)

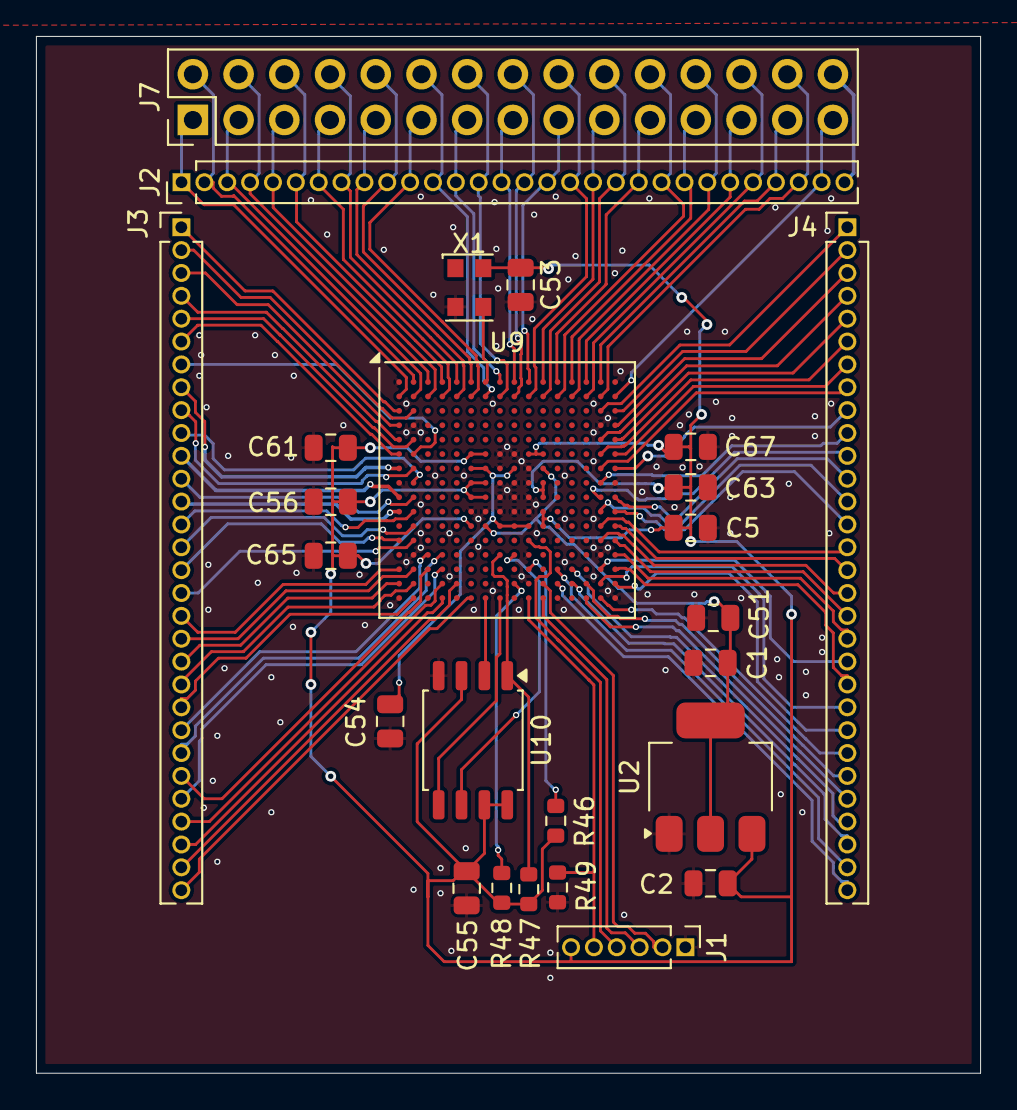
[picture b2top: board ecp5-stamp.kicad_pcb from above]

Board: 2 copper layers, 52.5 x 57.6 mm, 25 parts (0 on the bottom side), 105 nets.

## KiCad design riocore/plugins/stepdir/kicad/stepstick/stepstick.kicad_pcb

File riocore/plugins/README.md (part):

# PLUGINS

| Type | Name | Info | Image | Comment |
| --- | :---: | --- | :---: | :---: |
| Interfaces | [arty_mii](arty_mii/README.md) | udp interface for host comunication - Arty7-35t only |  | Experimental  |
|  | [ksz8851](ksz8851/README.md) | UDP interface for host communication |  |  |
|  | [rmii](rmii/README.md) | rmii udp interface |  | Experimental  |
|  | [spi](spi/README.md) | spi interface for host comunication |  |  |
|  | [spi_prog](spi_prog/README.md) | spi interface for host comunication and flash programming |  |  |
|  | [spibridge](spibridge/README.md) | spi interface for host comunication over UDB2SPI-Bridges |  |  |
|  | [uart](uart/README.md) | uart interface for host cominucation |  |  |
|  | [udp2axi](udp2axi/README.md) | udp2axi interface for armcore comunication |  | Experimental  |
|  | [w5500](w5500/README.md) | udp interface for host comunication |  |  |
|  | [arty_mii](arty_mii/README.md) | udp interface for host comunication - Arty7-35t only |  | Experimental  |
|  | [ksz8851](ksz8851/README.md) | UDP interface for host communication |  |  |
|  | [rmii](rmii/README.md) | rmii udp interface |  | Experimental  |
|  | [spi](spi/README.md) | spi interface for host comunication |  |  |
|  | [spi_prog](spi_prog/README.md) | spi interface for host comunication and flash programming |  |  |
|  | [spibridge](spibridge/README.md) | spi interface for host comunication over UDB2SPI-Bridges |  |  |
|  | [uart](uart/README.md) | uart interface for host cominucation |  |  |
|  | [udp2axi](udp2axi/README.md) | udp2axi interface for armcore comunication |  | Experimental  |
|  | [w5500](w5500/README.md) | udp interface for host comunication |  |  |
| Joints | [bldc](bldc/README.md) | BLDC FOC |  | Experimental  |
|  | [hbridge](hbridge/README.md) | hbridge output |  |  |
|  | [pdmout](pdmout/README.md) | pdm output |  |  |
|  | [pwmout](pwmout/README.md) | pwm output |  |  |
|  | [rcservo](rcservo/README.md) | rc-servo output |  |  |
|  | [riodrive](riodrive/README.md) | to control a riodrive via can-bus |  | Experimental  |
|  | [stepdir](stepdir/README.md) | step/dir output for stepper drivers |  |  |
|  | [stepgen](stepgen/README.md) | software step pulse generation |  |  |
|  | [stepper](stepper/README.md) | stepper driver output for H-Bridges like L298 |  |  |
|  | [tmc5160](tmc5160/README.md) | TMC5160 SPI joint |  | Experimental  |
|  | [bldc](bldc/README.md) | BLDC FOC |  | Experimental  |
|  | [hbridge](hbridge/README.md) | hbridge output |  |  |
|  | [pdmout](pdmout/README.md) | pdm output |  |  |
|  | [pwmout](pwmout/README.md) | pwm output |  |  |
|  | [rcservo](rcservo/README.md) | rc-servo output |  |  |
|  | [riodrive](riodrive/README.md) | to control a riodrive via can-bus |  | Experimental  |
|  | [stepdir](stepdir/README.md) | step/dir output for stepper drivers |  |  |
|  | [stepgen](stepgen/README.md) | software step pulse generation |  |  |
|  | [stepper](stepper/README.md) | stepper driver output for H-Bridges like L298 |  |  |
|  | [tmc5160](tmc5160/README.md) | TMC5160 SPI joint |  | Experimental  |
| IO | [abs_encoder](abs_encoder/README.md) | serial abs-encoder |  | Experimental  |
|  | [as5600pwm](as5600pwm/README.md) | as5600 pwm input |  |  |
|  | [binin](binin/README.md) | binary to decimal input |  |  |
|  | [binout](binout/README.md) | decimal to binary output |  |  |
|  | [bitcopy](bitcopy/README.md) | copy a bit/pin to an other output pin |  |  |
|  | [bitin](bitin/README.md) | single input pin |  |  |
|  | [bitout](bitout/README.md) | singe bit output pin |  |  |
|  | [blink](blink/README.md) | blinking output pin |  |  |
|  | [breakout](breakout/README.md) | 5Axis China-BOB |  |  |
|  | [caliper](caliper/README.md) | reading position from cheap calipers |  |  |
|  | [counter](counter/README.md) | pulse counter input |  |  |
|  | [demux](demux/README.md) | binary demultiplexer |  |  |
|  | [dis7seg](dis7seg/README.md) | 7segment display with buttons |  |  |
|  | [ds18b20](ds18b20/README.md) | 1Wire Temperature sensor |  |  |
|  | [encoder](encoder/README.md) | software counting of quadrature encoder signals |  |  |
|  | [flipflop_in](flipflop_in/README.md) | flipflop input |  |  |
|  | [flipflop_out](flipflop_out/README.md) | flipflop output |  |  |
|  | [freqin](freqin/README.md) | frequency input |  |  |
|  | [freqout](freqout/README.md) | frequency output |  |  |
|  | [gowin_empu](gowin_empu/README.md) | TangNano4K ARM core |  |  |
|  | [gpioin](gpioin/README.md) | gpio input |  |  |
|  | [gpioout](gpioout/README.md) | gpio output |  |  |
|  | [hallsensor](hallsensor/README.md) | bldc hallsensor |  |  |
|  | [hx710](hx710/README.md) | 24bit adc |  |  |
|  | [hx711](hx711/README.md) | digital weight sensor |  |  |
|  | [icewerxadc](icewerxadc/README.md) | 4-channel adc of the iceWerx-board |  |  |
|  | [interval](interval/README.md) | interval timer |  | Experimental  |
|  | [irin](irin/README.md) | IR-Remote input |  |  |
|  | [keymatrix](keymatrix/README.md) | Matix-Keyboard |  |  |
|  | [max10adc](max10adc/README.md) | MAX10 ADC inputs |  |  |
|  | [max6675](max6675/README.md) | SPI temperature sensor |  |  |
|  | [max7219](max7219/README.md) | 7segment display based on max7219 |  |  |
|  | [mcuio](mcuio/README.md) | mcu based io's |  |  |
|  | [mux](mux/README.md) | binary multiplexer |  |  |
|  | [pinroute](pinroute/README.md) | routing one output pin to multiple inputs |  |  |
|  | [prv32](prv32/README.md) | picorv32 based risc-v softcore |  | Experimental  |
|  | [pwmgen](pwmgen/README.md) | software PWM/PDM generation |  |  |
|  | [pwmin](pwmin/README.md) | pwm input |  |  |
|  | [quadencoder](quadencoder/README.md) | quadencoder |  |  |
|  | [quadencoderz](quadencoderz/README.md) | quadencoder with index pin |  |  |
|  | [serv](serv/README.md) | minimal risc-v softcore |  | Experimental  |
|  | [signal](signal/README.md) | virtual signal |  |  |
|  | [sinepwm](sinepwm/README.md) | sine pwm output |  |  |
|  | [sonar](sonar/README.md) | sonar sensor for distance measurement |  |  |
|  | [spipoti](spipoti/README.md) | spi digital poti |  |  |
|  | [tlc549c](tlc549c/README.md) | spi adc input |  |  |
|  | [tlc5615](tlc5615/README.md) | spi dac |  |  |
|  | [tm1638b8s7l8](tm1638b8s7l8/README.md) | 7segment display with buttons |  |  |
|  | [udpoti](udpoti/README.md) | digital-poti with up/down+dir interface |  |  |
|  | [wled](wled/README.md) | ws2812b interface |  |  |
|  | [wled_bar](wled_bar/README.md) | ws2812b interface for bar-displays |  |  |
|  | [abs_encoder](abs_encoder/README.md) | serial abs-encoder |  | Experimental  |
|  | [as5600pwm](as5600pwm/README.md) | as5600 pwm input |  |  |
|  | [binin](binin/README.md) | binary to decimal input |  |  |
|  | [binout](binout/README.md) | decimal to binary output |  |  |
|  | [bitcopy](bitcopy/README.md) | copy a bit/pin to an other output pin |  |  |
|  | [bitin](bitin/README.md) | single input pin |  |  |
|  | [bitout](bitout/README.md) | singe bit output pin |  |  |
|  | [blink](blink/README.md) | blinking output pin |  |  |
|  | [breakout](breakout/README.md) | 5Axis China-BOB |  |  |
|  | [caliper](caliper/README.md) | reading position from cheap calipers |  |  |
|  | [counter](counter/README.md) | pulse counter input |  |  |
|  | [demux](demux/README.md) | binary demultiplexer |  |  |
|  | [dis7seg](dis7seg/README.md) | 7segment display with buttons |  |  |
|  | [ds18b20](ds18b20/README.md) | 1Wire Temperature sensor |  |  |
|  | [encoder](encoder/README.md) | software counting of quadrature encoder signals |  |  |
|  | [flipflop_in](flipflop_in/README.md) | flipflop input |  |  |
|  | [flipflop_out](flipflop_out/README.md) | flipflop output |  |  |
|  | [freqin](freqin/README.md) | frequency input |  |  |
|  | [freqout](freqout/README.md) | frequency output |  |  |
|  | [gowin_empu](gowin_empu/README.md) | TangNano4K ARM core |  |  |
|  | [gpioin](gpioin/README.md) | gpio input |  |  |
|  | [gpioout](gpioout/README.md) | gpio output |  |  |
|  | [hallsensor](hallsensor/README.md) | bldc hallsensor |  |  |
|  | [hx710](hx710/README.md) | 24bit adc |  |  |
|  | [hx711](hx711/README.md) | digital weight sensor |  |  |
|  | [icewerxadc](icewerxadc/README.md) | 4-channel adc of the iceWerx-board |  |  |
|  | [interval](interval/README.md) | interval timer |  | Experimental  |
|  | [irin](irin/README.md) | IR-Remote input |  |  |
|  | [keymatrix](keymatrix/README.md) | Matix-Keyboard |  |  |
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
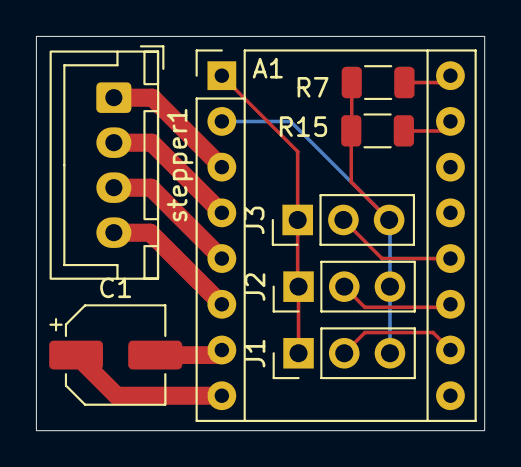
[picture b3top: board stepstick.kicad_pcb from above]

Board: 2 copper layers, 24.9 x 21.9 mm, 8 parts (0 on the bottom side), 13 nets.

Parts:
A1: Pololu_Breakout_A4988; Pololu_Breakout-16_15.2x20.3mm
C1: C_Polarized; CP_Elec_5x5.9
J1, J2, J3: Conn_01x03; PinHeader_1x03_P2.54mm_Vertical
R7, R15: 3k3; R_1206_3216Metric
stepper1: Conn_01x04; JST_XH_B4B-XH-A_1x04_P2.50mm_Vertical

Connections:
+3V3: A1.2 (VDD), J1.3, J2.3, J3.3, R7.2, R15.2
+12V: A1.8 (VMOT), C1.1
/dir: A1.16 (DIR), R7.1
/step: A1.15 (STEP), R15.1
GND: A1.1 (GND), A1.7 (GND), C1.2, J1.1, J2.1, J3.1
unnamed: A1.4 (1A), stepper1.2
unnamed: A1.3 (1B), stepper1.1
unnamed: A1.5 (2A), stepper1.3
unnamed: A1.6 (2B), stepper1.4
unnamed: A1.10 (MS1), J1.2
unnamed: A1.11 (MS2), J2.2
unnamed: A1.12 (MS3), J3.2
unnamed: A1.13 (~RESET), A1.14 (~SLEEP)

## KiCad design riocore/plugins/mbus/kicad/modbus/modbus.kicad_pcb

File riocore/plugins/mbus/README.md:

# mbus

**modbus plugin**

to read and write values (analog/digital) via modbus, also supports hy_vfd spindles

* Keywords: modbus rtu vfd spindle expansion analog digital
* URL: https://www.modbustools.com/modbus.html#function16
* NEEDS: fpga
* PROVIDES: modbus

## Pins:
*FPGA-pins*
### rx:

 * direction: input

### tx:

 * direction: output

### tx_enable:

 * direction: output

### BUS:IO:

 * direction: output

## Options:
*user-options*
### name:
name of this plugin instance

 * type: str
 * default: 

### image:
hardware type

 * type: imgselect
 * default: generic

### baud:
serial baud rate

 * type: int
 * min: 300
 * max: 10000000
 * default: 9600
 * unit: bit/s

### rx_buffersize:
max rx buffer size

 * type: int
 * min: 32
 * max: 255
 * default: 128
 * unit: bits

### tx_buffersize:
max tx buffer size

 * type: int
 * min: 32
 * max: 255
 * default: 128
 * unit: bits

## Signals:
*signals/pins in LinuxCNC*

## Interfaces:
*transport layer*
### rxdata:

 * size: 128 bit
 * direction: input

### txdata:

 * size: 128 bit
 * direction: output

## Verilogs:
 * [mbus.v](mbus.v)
 * [uart_baud.v](uart_baud.v)
 * [uart_rx.v](uart_rx.v)
 * [uart_tx.v](uart_tx.v)

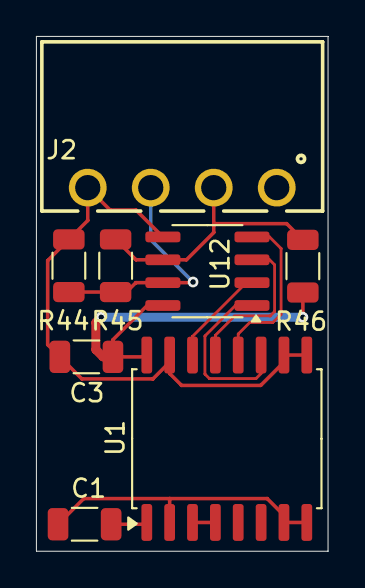
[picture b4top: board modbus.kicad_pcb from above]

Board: 2 copper layers, 16.2 x 28.6 mm, 8 parts (0 on the bottom side), 11 nets.

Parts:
C1, C3: 100n; C_1206_3216Metric
J2: modbus; 691322110004
R44, R46: 20k; R_1206_3216Metric
R45: 120; R_1206_3216Metric
U1: ADuM1411; SOIC-16W_7.5x10.3mm_P1.27mm
U12: MAX485E; SOIC-8_3.9x4.9mm_P1.27mm

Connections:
+3.3V: C1.1, U1.1 (VDD1)
/tx_enable: U1.3 (VIA), U1.4 (VIB)
F_5V: C3.1, R46.1, U1.16 (VDD2), U12.8 (VCC)
F_GND: C3.2, J2.4, R44.2, U1.9 (GND2), U1.10 (CTRL2), U1.15 (GND2), U12.5 (GND)
GND: C1.2, U1.2 (GND1), U1.7 (CTRL1), U1.8 (GND1)
unnamed: U1.11 (VID), U12.1 (RO)
unnamed: U1.14 (VOA), U12.2 (~RE)
unnamed: U1.13 (VOB), U12.3 (DE)
unnamed: U1.12 (VOC), U12.4 (DI)
unnamed: J2.2, R45.1, R46.2, U12.6 (A)
unnamed: J2.3, R44.1, R45.2, U12.7 (B)

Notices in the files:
README.md:
./doc/images/license-GPL2-blue.svg
